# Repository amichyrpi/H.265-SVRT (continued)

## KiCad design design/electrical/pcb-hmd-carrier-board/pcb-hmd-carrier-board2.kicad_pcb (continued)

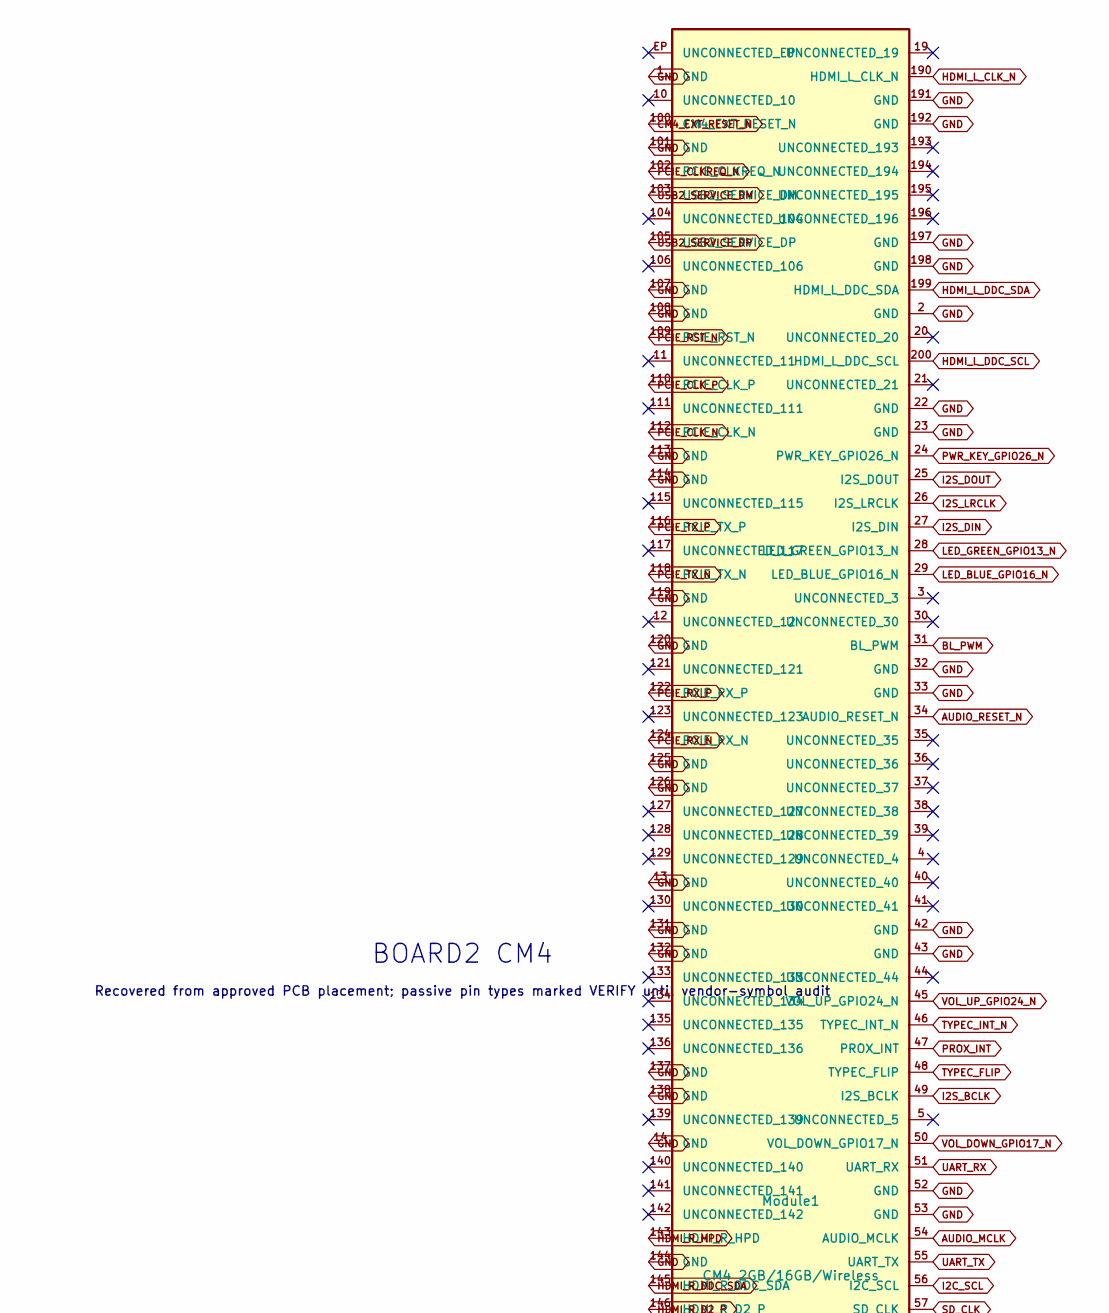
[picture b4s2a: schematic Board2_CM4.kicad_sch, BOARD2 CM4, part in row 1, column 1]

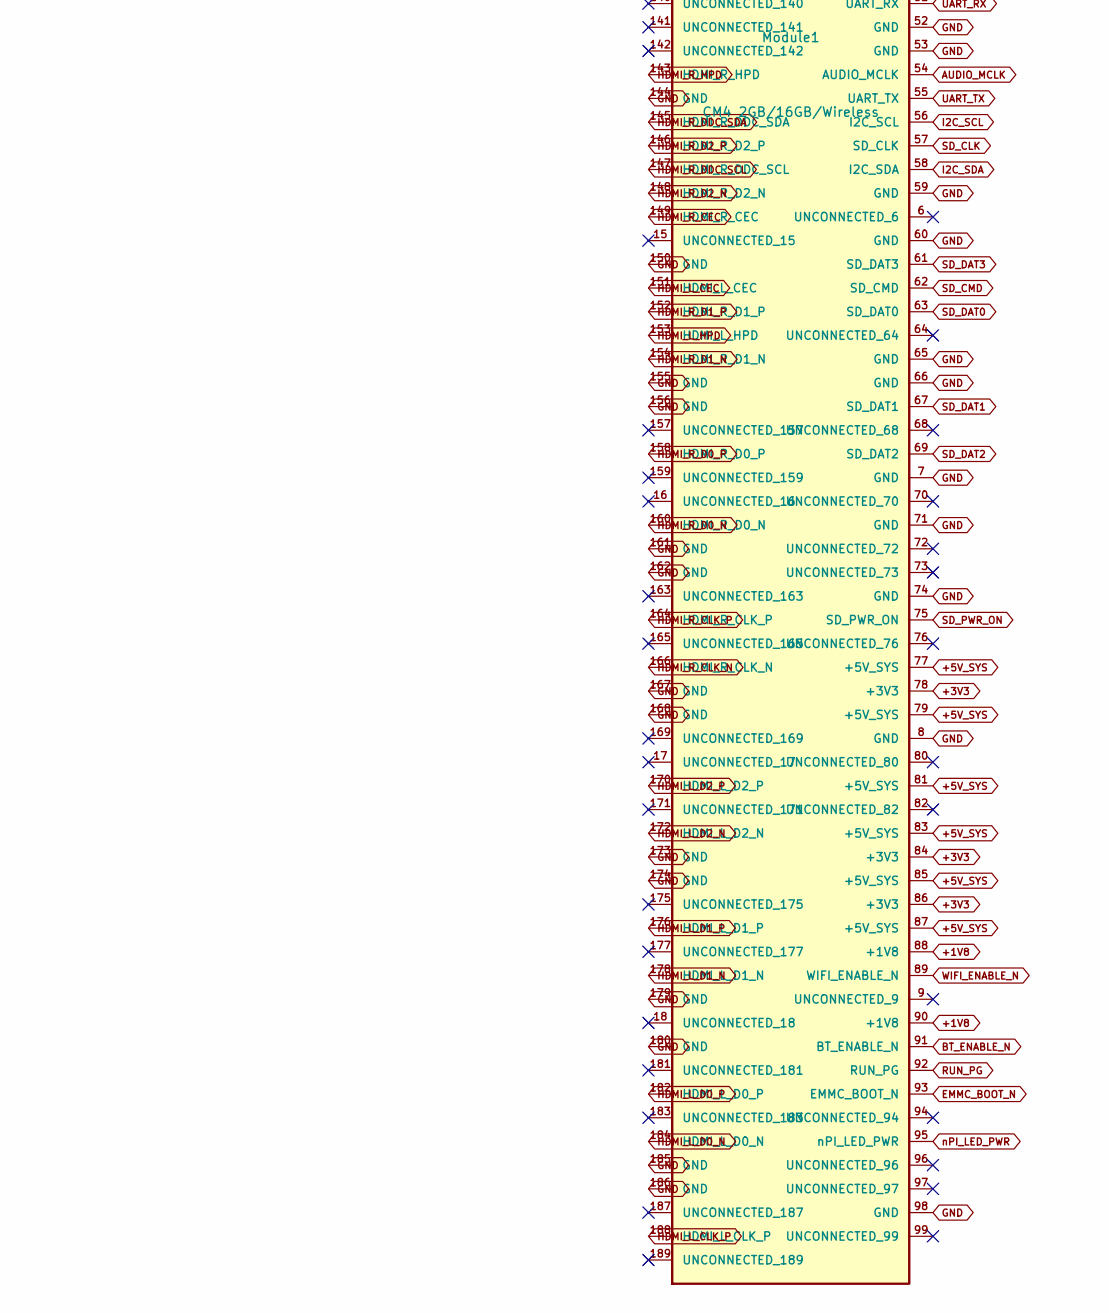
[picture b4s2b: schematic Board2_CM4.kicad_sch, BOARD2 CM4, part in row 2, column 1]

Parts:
Module1: CM4 2GB/16GB/Wireless; Raspberry-Pi-4-Compute-Module

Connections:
+1V8: Module1.88 (+1V8), Module1.90 (+1V8)
+3V3: Module1.78 (+3V3), Module1.84 (+3V3), Module1.86 (+3V3); also elsewhere on the board
+5V_SYS: Module1.77 (+5V_SYS), Module1.79 (+5V_SYS), Module1.81 (+5V_SYS), Module1.83 (+5V_SYS), Module1.85 (+5V_SYS), Module1.87 (+5V_SYS); also elsewhere on the board
AUDIO_MCLK: Module1.54 (AUDIO_MCLK); also elsewhere on the board
AUDIO_RESET_N: Module1.34 (AUDIO_RESET_N); also elsewhere on the board
BL_PWM: Module1.31 (BL_PWM); also elsewhere on the board
BT_ENABLE_N: Module1.91 (BT_ENABLE_N); also elsewhere on the board
CM4_EXT_RESET_N: Module1.100 (CM4_EXT_RESET_N); also elsewhere on the board
EMMC_BOOT_N: Module1.93 (EMMC_BOOT_N); also elsewhere on the board
GND: Module1.1 (GND), Module1.2 (GND), Module1.7 (GND), Module1.8 (GND), Module1.13 (GND), Module1.14 (GND), Module1.22 (GND), Module1.23 (GND), Module1.32 (GND), Module1.33 (GND), Module1.42 (GND), Module1.43 (GND), Module1.52 (GND), Module1.53 (GND), Module1.59 (GND), Module1.60 (GND), Module1.65 (GND), Module1.66 (GND), Module1.71 (GND), Module1.74 (GND), Module1.98 (GND), Module1.101 (GND), Module1.107 (GND), Module1.108 (GND), Module1.113 (GND), Module1.114 (GND), Module1.119 (GND), Module1.120 (GND), Module1.125 (GND), Module1.126 (GND), Module1.131 (GND), Module1.132 (GND), Module1.137 (GND), Module1.138 (GND), Module1.144 (GND), Module1.150 (GND), Module1.155 (GND), Module1.156 (GND), Module1.161 (GND), Module1.162 (GND), Module1.167 (GND), Module1.168 (GND), Module1.173 (GND), Module1.174 (GND), Module1.179 (GND), Module1.180 (GND), Module1.185 (GND), Module1.186 (GND), Module1.191 (GND), Module1.192 (GND), Module1.197 (GND), Module1.198 (GND); also elsewhere on the board
HDMI_L_CEC: Module1.151 (HDMI_L_CEC); also elsewhere on the board
HDMI_L_CLK_N: Module1.190 (HDMI_L_CLK_N); also elsewhere on the board
HDMI_L_CLK_P: Module1.188 (HDMI_L_CLK_P); also elsewhere on the board
HDMI_L_D0_N: Module1.184 (HDMI_L_D0_N); also elsewhere on the board
HDMI_L_D0_P: Module1.182 (HDMI_L_D0_P); also elsewhere on the board
HDMI_L_D1_N: Module1.178 (HDMI_L_D1_N); also elsewhere on the board
HDMI_L_D1_P: Module1.176 (HDMI_L_D1_P); also elsewhere on the board
HDMI_L_D2_N: Module1.172 (HDMI_L_D2_N); also elsewhere on the board
HDMI_L_D2_P: Module1.170 (HDMI_L_D2_P); also elsewhere on the board
HDMI_L_DDC_SCL: Module1.200 (HDMI_L_DDC_SCL); also elsewhere on the board
HDMI_L_DDC_SDA: Module1.199 (HDMI_L_DDC_SDA); also elsewhere on the board
HDMI_L_HPD: Module1.153 (HDMI_L_HPD); also elsewhere on the board
HDMI_R_CEC: Module1.149 (HDMI_R_CEC); also elsewhere on the board
HDMI_R_CLK_N: Module1.166 (HDMI_R_CLK_N); also elsewhere on the board
HDMI_R_CLK_P: Module1.164 (HDMI_R_CLK_P); also elsewhere on the board
HDMI_R_D0_N: Module1.160 (HDMI_R_D0_N); also elsewhere on the board
HDMI_R_D0_P: Module1.158 (HDMI_R_D0_P); also elsewhere on the board
HDMI_R_D1_N: Module1.154 (HDMI_R_D1_N); also elsewhere on the board
HDMI_R_D1_P: Module1.152 (HDMI_R_D1_P); also elsewhere on the board
HDMI_R_D2_N: Module1.148 (HDMI_R_D2_N); also elsewhere on the board
HDMI_R_D2_P: Module1.146 (HDMI_R_D2_P); also elsewhere on the board
HDMI_R_DDC_SCL: Module1.147 (HDMI_R_DDC_SCL); also elsewhere on the board
HDMI_R_DDC_SDA: Module1.145 (HDMI_R_DDC_SDA); also elsewhere on the board
HDMI_R_HPD: Module1.143 (HDMI_R_HPD); also elsewhere on the board
I2C_SCL: Module1.56 (I2C_SCL); also elsewhere on the board
I2C_SDA: Module1.58 (I2C_SDA); also elsewhere on the board
I2S_BCLK: Module1.49 (I2S_BCLK); also elsewhere on the board
I2S_DIN: Module1.27 (I2S_DIN); also elsewhere on the board
I2S_DOUT: Module1.25 (I2S_DOUT); also elsewhere on the board
I2S_LRCLK: Module1.26 (I2S_LRCLK); also elsewhere on the board
LED_BLUE_GPIO16_N: Module1.29 (LED_BLUE_GPIO16_N); also elsewhere on the board
LED_GREEN_GPIO13_N: Module1.28 (LED_GREEN_GPIO13_N); also elsewhere on the board
PCIE_CLKREQ_N: Module1.102 (PCIE_CLKREQ_N); also elsewhere on the board
PCIE_CLK_N: Module1.112 (PCIE_CLK_N); also elsewhere on the board
PCIE_CLK_P: Module1.110 (PCIE_CLK_P); also elsewhere on the board
PCIE_RST_N: Module1.109 (PCIE_RST_N); also elsewhere on the board
PCIE_RX_N: Module1.124 (PCIE_RX_N); also elsewhere on the board
PCIE_RX_P: Module1.122 (PCIE_RX_P); also elsewhere on the board
PCIE_TX_N: Module1.118 (PCIE_TX_N); also elsewhere on the board
PCIE_TX_P: Module1.116 (PCIE_TX_P); also elsewhere on the board
PROX_INT: Module1.47 (PROX_INT); also elsewhere on the board
PWR_KEY_GPIO26_N: Module1.24 (PWR_KEY_GPIO26_N); also elsewhere on the board
RUN_PG: Module1.92 (RUN_PG); also elsewhere on the board
SD_CLK: Module1.57 (SD_CLK); also elsewhere on the board
SD_CMD: Module1.62 (SD_CMD); also elsewhere on the board
SD_DAT0: Module1.63 (SD_DAT0); also elsewhere on the board
SD_DAT1: Module1.67 (SD_DAT1); also elsewhere on the board
SD_DAT2: Module1.69 (SD_DAT2); also elsewhere on the board
SD_DAT3: Module1.61 (SD_DAT3); also elsewhere on the board
SD_PWR_ON: Module1.75 (SD_PWR_ON); also elsewhere on the board
TYPEC_FLIP: Module1.48 (TYPEC_FLIP); also elsewhere on the board
TYPEC_INT_N: Module1.46 (TYPEC_INT_N); also elsewhere on the board
UART_RX: Module1.51 (UART_RX); also elsewhere on the board
UART_TX: Module1.55 (UART_TX); also elsewhere on the board
USB2_SERVICE_DM: Module1.103 (USB2_SERVICE_DM); also elsewhere on the board
USB2_SERVICE_DP: Module1.105 (USB2_SERVICE_DP); also elsewhere on the board
VOL_DOWN_GPIO17_N: Module1.50 (VOL_DOWN_GPIO17_N); also elsewhere on the board
VOL_UP_GPIO24_N: Module1.45 (VOL_UP_GPIO24_N); also elsewhere on the board
WIFI_ENABLE_N: Module1.89 (WIFI_ENABLE_N); also elsewhere on the board
nPI_LED_PWR: Module1.95 (nPI_LED_PWR); also elsewhere on the board

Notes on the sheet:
BOARD2 CM4
Recovered from approved PCB placement; passive pin types marked VERIFY until vendor-symbol audit

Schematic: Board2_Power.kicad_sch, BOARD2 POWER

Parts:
C4, C5, C9, C10, C11, C19, C20, C21, C22, C23: 10u; C_0603_1608Metric
C6, C12, C24, C25: 100n; C_0603_1608Metric
C16: 4u7; C_0603_1608Metric
C26: 1u; C_0603_1608Metric
C57, C58: 100u low-ESR; C_0603_1608Metric
C59, C60: 22u 25V; C_0603_1608Metric
C2031, C2041, C2051, C2061: 4.7uF 10V; C_0603_1608Metric
L2: SRP7050TA-2R2M 2.2uH 10A; Bourns_SRP7050TA
R1: 220k; R_0402_1005Metric
R3: 5.23k ILIM; R_0402_1005Metric
R8: 10k; R_0402_1005Metric
R11: 100R BATP; R_0402_1005Metric
R24: 75k MODE; R_0402_1005Metric
R27: 2.2k CHG SCL; R_0402_1005Metric
R28: 2.2k CHG SDA; R_0402_1005Metric
U2: TPS568230RJER; Texas_RJE0020A_VQFN-20-1EP_3x3mm_P0.45mm_EP0.675x0.76mm_The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
U6: BQ25798RQMR; Texas_RQM0029A_VQFN-29_4x4mm_P0.4mm
U12: TPS25751DREFR; Texas_REF0038A_WQFN-38_6x4mm_DualPad

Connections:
+3V3: R8.1 (+3V3), U12.38 (+3V3); also elsewhere on the board
+5V_SYS: C57.1 (+5V_SYS), C58.1 (+5V_SYS), C2031.1 (+5V_SYS), C2041.1 (+5V_SYS), C2051.1 (+5V_SYS), C2061.1 (+5V_SYS), L2.2 (+5V_SYS), R1.1 (+5V_SYS), U12.34 (+5V_SYS), U12.35 (+5V_SYS); also elsewhere on the board
BAT+: C24.1 (BAT+), R11.2 (BAT+), U6.22 (BAT+), U6.23 (BAT+)
BATP: R11.1 (BATP), U6.18 (BATP)
BST1: U6.4 (BST1); also elsewhere on the board
BST2: U6.19 (BST2); also elsewhere on the board
BST_5V: C25.1 (BST_5V), U2.1 (BST_5V)
CC1: U12.28 (CC1); also elsewhere on the board
CC2: U12.29 (CC2); also elsewhere on the board
CHG_IRQ_N: R8.2 (CHG_IRQ_N), U6.21 (CHG_IRQ_N), U12.18 (CHG_IRQ_N)
CHG_SCL: R27.2 (CHG_SCL), U6.14 (CHG_SCL), U12.17 (CHG_SCL)
CHG_SDA: R28.2 (CHG_SDA), U6.15 (CHG_SDA), U12.16 (CHG_SDA)
CHG_STAT: U6.1 (CHG_STAT); also elsewhere on the board
FB_5V: R1.2 (FB_5V), U2.14 (FB_5V); also elsewhere on the board
GND: C4.2 (GND), C5.2 (GND), C6.2 (GND), C9.2 (GND), C10.2 (GND), C11.2 (GND), C12.2 (GND), C16.2 (GND), C19.2 (GND), C20.2 (GND), C21.2 (GND), C22.2 (GND), C23.2 (GND), C24.2 (GND), C26.2 (GND), C57.2 (GND), C58.2 (GND), C59.2 (GND), C60.2 (GND), C2031.2 (GND), C2041.2 (GND), C2051.2 (GND), C2061.2 (GND), U2.7 (GND), U2.8 (GND), U2.13 (GND), U2.18 (GND), U2.21 (GND), U6.10 (GND), U6.11 (GND), U6.12 (GND), U6.13 (GND), U6.27 (GND), U12.11 (GND), U12.12 (GND), U12.14 (GND), U12.31 (GND), U12.39 (GND); also elsewhere on the board
I2Ct_SCL: U12.9 (I2Ct_SCL); also elsewhere on the board
I2Ct_SDA: U12.8 (I2Ct_SDA); also elsewhere on the board
ILIM_HIZ: R3.2 (ILIM_HIZ), U6.17 (ILIM_HIZ); also elsewhere on the board
LDO_1V5: U12.2 (LDO_1V5), U12.3 (LDO_1V5), U12.4 (LDO_1V5); also elsewhere on the board
LDO_3V3: R27.1 (LDO_3V3), R28.1 (LDO_3V3), U12.1 (LDO_3V3); also elsewhere on the board
MODE_5V: R24.2 (MODE_5V), U2.15 (MODE_5V); also elsewhere on the board
PD_IRQ_N: U12.10 (PD_IRQ_N); also elsewhere on the board
PGOOD_5V: U2.9 (PGOOD_5V); also elsewhere on the board
PMID: U6.29 (PMID); also elsewhere on the board
PPHV: C4.1 (PPHV), C5.1 (PPHV), C6.1 (PPHV), U6.2 (PPHV), U6.3 (PPHV), U6.8 (PPHV), U6.9 (PPHV), U12.20 (PPHV), U12.21 (PPHV), U12.22 (PPHV)
PROG: U6.20 (PROG); also elsewhere on the board
REGN: C16.1 (REGN), R3.1 (REGN), U6.5 (REGN)
SW1: U6.28 (SW1); also elsewhere on the board
SW2: U6.26 (SW2); also elsewhere on the board
SW_5V: C25.2 (SW_5V), L2.1 (SW_5V), U2.6 (SW_5V), U2.19 (SW_5V), U2.20 (SW_5V)
TS: U6.16 (TS); also elsewhere on the board
USB2_SERVICE_DM: U12.27 (USB2_SERVICE_DM); also elsewhere on the board
USB2_SERVICE_DP: U12.26 (USB2_SERVICE_DP); also elsewhere on the board
VBAT_SYS: C19.1 (VBAT_SYS), C20.1 (VBAT_SYS), C21.1 (VBAT_SYS), C22.1 (VBAT_SYS), C23.1 (VBAT_SYS), C59.1 (VBAT_SYS), C60.1 (VBAT_SYS), U2.2 (VBAT_SYS), U2.3 (VBAT_SYS), U2.4 (VBAT_SYS), U2.5 (VBAT_SYS), U2.12 (VBAT_SYS), U6.25 (VBAT_SYS); also elsewhere on the board
VBUS_CHARGE: C9.1 (VBUS_CHARGE), C10.1 (VBUS_CHARGE), C11.1 (VBUS_CHARGE), C12.1 (VBUS_CHARGE), U12.23 (VBUS_CHARGE), U12.24 (VBUS_CHARGE), U12.25 (VBUS_CHARGE), U12.32 (VBUS_CHARGE), U12.33 (VBUS_CHARGE); also elsewhere on the board
VCC_5V: C26.1 (VCC_5V), R24.1 (VCC_5V), U2.17 (VCC_5V)

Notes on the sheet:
BOARD2 POWER
Recovered from approved PCB placement; passive pin types marked VERIFY until vendor-symbol audit

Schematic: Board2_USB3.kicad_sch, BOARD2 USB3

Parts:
C28, C29, C30, C31, C32, C33, C34, C35, C36, C37: 100n; C_0402_1005Metric
C38: 10u; C_0402_1005Metric
C39, C40: 1u; C_0402_1005Metric
C55, C56: 100n PCIe AC; C_0402_1005Metric
C68: 100n USB3 RESET; C_0402_1005Metric
J8: DX07S024JJ2R1300 ACCESSORY; JAE_DX07S024JJ2R1300
R13, R14: 200k; R_0402_1005Metric
R15: ILIM 1.5A TBD; R_0402_1005Metric
R26: 10k CLKREQ; R_0402_1005Metric
R29: 10k OCI PU; R_0402_1005Metric
R30: 1.6k RREF VERIFY; R_0402_1005Metric
R31: 10k RESET PU; R_0402_1005Metric
R32: 10k SPI CLK PD; R_0402_1005Metric
R33: 10k SPI CS PD; R_0402_1005Metric
R34: 10k SPI MISO PU; R_0402_1005Metric
R35: 10k SPI MOSI PD; R_0402_1005Metric
U5: TUSB320LAIRWBR; Texas_X2QFN-12_1.6x1.6mm_P0.4mm
U7: TPD2EUSB30DRTR; SOT-23
U8, U9: TPD4EUSB30DQAR; USON-10_2.5x1.0mm_P0.5mm
U11: HD3SS3212IRKSR; Texas_RVC0020A_WQFN-20-1EP_3x4mm_P0.5mm_EP1.6x2.6mm
U14: UPD720202K8-711-BAA-A; QFN-48-1EP_7x7mm_P0.5mm_EP5.7x5.7mm_ThermalVias
U15: TLV803EA30DBZR; SOT-23
U16: TPS2553-1DRVR; WSON-6-1EP_2x2mm_P0.65mm_EP1x1.6mm
Y1: 24MHz; Crystal_SMD_3225-4Pin_3.2x2.5mm

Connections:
+1V05_USB: C28.1 (+1V05_USB), C29.1 (+1V05_USB), C30.1 (+1V05_USB), C31.1 (+1V05_USB), C32.1 (+1V05_USB), C33.1 (+1V05_USB), C39.1 (+1V05_USB), U14.6 (+1V05_USB), U14.9 (+1V05_USB), U14.21 (+1V05_USB), U14.30 (+1V05_USB), U14.33 (+1V05_USB), U14.39 (+1V05_USB), U14.42 (+1V05_USB); also elsewhere on the board
+3V3: C34.1 (+3V3), C35.1 (+3V3), C36.1 (+3V3), C37.1 (+3V3), C38.1 (+3V3), C40.1 (+3V3), C68.1 (+3V3), R13.1 (+3V3), R14.1 (+3V3), R26.1 (+3V3), R29.1 (+3V3), R31.1 (+3V3), R34.1 (+3V3), U5.3 (+3V3), U5.12 (+3V3), U11.6 (+3V3), U14.3 (+3V3), U14.12 (+3V3), U14.22 (+3V3), U14.25 (+3V3), U14.34 (+3V3), U14.43 (+3V3), U15.3 (+3V3); also elsewhere on the board
+5V_SYS: U16.6 (+5V_SYS); also elsewhere on the board
CC1: J8.A5 (CC1), U5.1 (CC1); also elsewhere on the board
CC2: J8.B5 (CC2), U5.2 (CC2); also elsewhere on the board
GND: C28.2 (GND), C29.2 (GND), C30.2 (GND), C31.2 (GND), C32.2 (GND), C33.2 (GND), C34.2 (GND), C35.2 (GND), C36.2 (GND), C37.2 (GND), C38.2 (GND), C39.2 (GND), C40.2 (GND), C68.2 (GND), J8.A1 (GND), J8.A12 (GND), J8.B1 (GND), J8.B12 (GND), J8.SH (GND), R15.2 (GND), R30.2 (GND), R32.2 (GND), R33.2 (GND), R35.2 (GND), U5.5 (GND), U5.10 (GND), U5.11 (GND), U7.3 (GND), U8.3 (GND), U8.8 (GND), U9.3 (GND), U9.8 (GND), U11.2 (GND), U11.5 (GND), U11.11 (GND), U11.20 (GND), U14.27 (GND), U14.49 (GND), U15.1 (GND), U16.5 (GND), U16.7 (GND), Y1.2 (GND), Y1.4 (GND); also elsewhere on the board
I2C_SCL: U5.8 (I2C_SCL); also elsewhere on the board
I2C_SDA: U5.7 (I2C_SDA); also elsewhere on the board
PCIE_CLKREQ_N: R26.2 (PCIE_CLKREQ_N), U14.10 (PCIE_CLKREQ_N); also elsewhere on the board
PCIE_CLK_N: U14.2 (PCIE_CLK_N); also elsewhere on the board
PCIE_CLK_P: U14.1 (PCIE_CLK_P); also elsewhere on the board
PCIE_RST_N: U14.47 (PCIE_RST_N); also elsewhere on the board
PCIE_RX_N: C56.2 (PCIE_RX_N); also elsewhere on the board
PCIE_RX_P: C55.2 (PCIE_RX_P); also elsewhere on the board
PCIE_RX_USB3_N: C56.1 (PCIE_RX_USB3_N), U14.5 (PCIE_RX_USB3_N)
PCIE_RX_USB3_P: C55.1 (PCIE_RX_USB3_P), U14.4 (PCIE_RX_USB3_P)
PCIE_TX_N: U14.8 (PCIE_TX_N); also elsewhere on the board
PCIE_TX_P: U14.7 (PCIE_TX_P); also elsewhere on the board
SPI_CLK: R32.1 (SPI_CLK), U14.15 (SPI_CLK)
SPI_CS_N: R33.1 (SPI_CS_N), U14.14 (SPI_CS_N)
SPI_MISO: R34.2 (SPI_MISO), U14.13 (SPI_MISO)
SPI_MOSI: R35.1 (SPI_MOSI), U14.16 (SPI_MOSI)
TYPEC_ATTACHED_N: R14.2 (TYPEC_ATTACHED_N), U5.9 (TYPEC_ATTACHED_N), U16.4 (TYPEC_ATTACHED_N)
TYPEC_FLIP: U11.9 (TYPEC_FLIP); also elsewhere on the board
TYPEC_INT_N: R13.2 (TYPEC_INT_N), U5.6 (TYPEC_INT_N); also elsewhere on the board
USB2_HOST_DM: J8.A7 (USB2_HOST_DM), J8.B7 (USB2_HOST_DM), U7.2 (USB2_HOST_DM), U14.36 (USB2_HOST_DM)
USB2_HOST_DP: J8.A6 (USB2_HOST_DP), J8.B6 (USB2_HOST_DP), U7.1 (USB2_HOST_DP), U14.35 (USB2_HOST_DP)
USB3_POR_N: R31.2 (USB3_POR_N), U14.11 (USB3_POR_N), U15.2 (USB3_POR_N)
USB3_RREF: R30.1 (USB3_RREF), U14.26 (USB3_RREF)
USB3_RX_N: U11.8 (USB3_RX_N), U14.32 (USB3_RX_N)
USB3_RX_P: U11.7 (USB3_RX_P), U14.31 (USB3_RX_P)
USB3_TX_N: U11.4 (USB3_TX_N), U14.29 (USB3_TX_N)
USB3_TX_P: U11.3 (USB3_TX_P), U14.28 (USB3_TX_P)
USB3_XT1: U14.24 (USB3_XT1), Y1.1 (USB3_XT1)
USB3_XT2: U14.23 (USB3_XT2), Y1.3 (USB3_XT2)
USB_C_RX1_N: J8.B10 (USB_C_RX1_N), U8.5 (USB_C_RX1_N), U11.16 (USB_C_RX1_N)
USB_C_RX1_P: J8.B11 (USB_C_RX1_P), U8.4 (USB_C_RX1_P), U11.17 (USB_C_RX1_P)
USB_C_RX2_N: J8.A10 (USB_C_RX2_N), U9.5 (USB_C_RX2_N), U11.12 (USB_C_RX2_N)
USB_C_RX2_P: J8.A11 (USB_C_RX2_P), U9.4 (USB_C_RX2_P), U11.13 (USB_C_RX2_P)
USB_C_TX1_N: J8.A3 (USB_C_TX1_N), U8.2 (USB_C_TX1_N), U11.18 (USB_C_TX1_N)
USB_C_TX1_P: J8.A2 (USB_C_TX1_P), U8.1 (USB_C_TX1_P), U11.19 (USB_C_TX1_P)
USB_C_TX2_N: J8.B3 (USB_C_TX2_N), U9.2 (USB_C_TX2_N), U11.14 (USB_C_TX2_N)
USB_C_TX2_P: J8.B2 (USB_C_TX2_P), U9.1 (USB_C_TX2_P), U11.15 (USB_C_TX2_P)
USB_ILIM: R15.1 (USB_ILIM), U16.2 (USB_ILIM)
USB_OC_N: R29.2 (USB_OC_N), U14.19 (USB_OC_N), U16.3 (USB_OC_N)
VBUS_USB_HOST: J8.A4 (VBUS_USB_HOST), J8.A9 (VBUS_USB_HOST), J8.B4 (VBUS_USB_HOST), J8.B9 (VBUS_USB_HOST), U16.1 (VBUS_USB_HOST)

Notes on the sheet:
BOARD2 USB3
Recovered from approved PCB placement; passive pin types marked VERIFY until vendor-symbol audit
